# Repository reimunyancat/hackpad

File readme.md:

# Hackpad — 9-Key Macropad

A custom 9-key (3x3 matrix) macropad with a rotary encoder and a 1.3" OLED, built for the Hack Club Stardance Hackpad YSWS.

- **MCU:** Seeed XIAO RP2040
- **Layout:** 3x3 switch matrix + 1 rotary encoder (EC11) + 1.3" 128x64 OLED (I2C)
- **Firmware:** KMK (CircuitPython)
- **Case:** Sandwich-style, fully 3D printed

## Gallery

### Assembled model

### Schematic

### PCB layout

### Case (3D)

## Bill of Materials

| Component | Qty | Notes |
| --- | --- | --- |
| Seeed XIAO RP2040 | 1 | MCU (kit) |
| 1N4148 diode | 9 | matrix anti-ghosting (kit) |
| MX-style switch | 9 | (kit) |
| Kailh MX hotswap socket | 9 | self-sourced |
| EC11 rotary encoder | 1 | 20mm D-shaft (kit) |
| 1.3" 128x64 SH1106 OLED | 1 | I2C, self-sourced |
| 2.54mm 4-pin female header | 1 | OLED mount, self-sourced |
| DSA keycap | 9 | (kit) |
| M3x16 screw | 6 | (kit) |
| M3x5x4 heatset insert | 6 | (kit) |
| Custom PCB | 1 | JLCPCB, 2-layer, ~57x79mm |
| 3D printed case | 1 | top plate + bottom shell |

## Repository structure

```
.
├── README.md
├── CAD/
│   └── assembled-model.STEP
├── PCB/
│   ├── hackpad.kicad_pro
│   ├── hackpad.kicad_sch
│   └── hackpad.kicad_pcb
├── Firmware/
│   └── main.py
└── production/
    ├── gerbers.zip
    ├── Top.STEP
    ├── Bottom.STEP
    └── main.py
```

## Firmware

KMK (CircuitPython). Flash CircuitPython to the XIAO, copy the `kmk` library folder onto the CIRCUITPY drive, then drop `Firmware/main.py` on it.

Pin mapping (taken from the schematic):

- Columns: D0, D1, D2
- Rows: D3, D6, D7
- Encoder: A = D8, B = D9, SW = D10
- OLED I2C: SDA = D4, SCL = D5
- Diode orientation: COL2ROW

## Specs

- PCB: ~57x79mm, 2-layer (limit 100x100mm)
- Case: fully 3D printed (limit 200x200x100mm)
- Inputs: 9 keys + 1 encoder = 10 (limit 16)
- Tolerances: 0.2mm on mating surfaces, M3x5x4 heatset inserts (4.7mm holes), M3x16 screws (3.4mm clearance)

Note: I need a soldering iron — please include the $18 soldering iron grant.

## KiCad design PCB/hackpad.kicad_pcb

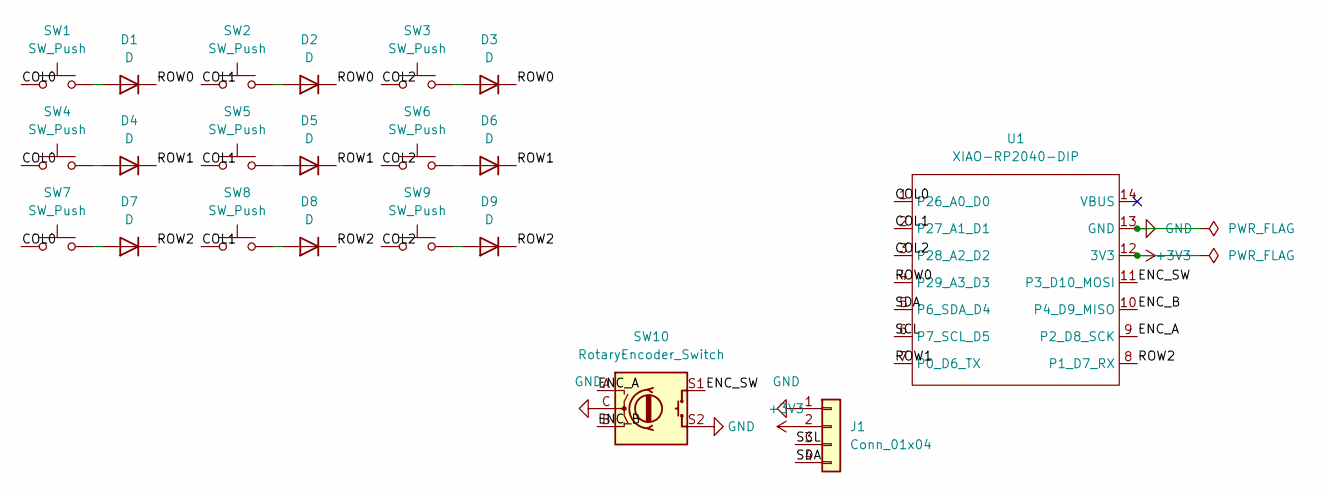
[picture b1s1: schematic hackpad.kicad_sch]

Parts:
D1, D2, D3, D4, D5, D6, D7, D8, D9: D; D_DO-35_SOD27_P7.62mm_Horizontal
J1: Conn_01x04; PinHeader_1x04_P2.54mm_Vertical
SW1, SW2, SW3, SW4, SW5, SW6, SW7, SW8, SW9: SW_Push; Kailh_socket_MX
SW10: RotaryEncoder_Switch; RotaryEncoder_Alps_EC11E-Switch_Vertical_H20mm
U1: XIAO-RP2040-DIP

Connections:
+3V3: J1.2, U1.12 (3V3)
/COL0: SW1.1, SW4.1, SW7.1, U1.1 (P26_A0_D0)
/COL1: SW2.1, SW5.1, SW8.1, U1.2 (P27_A1_D1)
/COL2: SW3.1, SW6.1, SW9.1, U1.3 (P28_A2_D2)
/ENC_A: SW10.A, U1.9 (P2_D8_SCK)
/ENC_B: SW10.B, U1.10 (P4_D9_MISO)
/ENC_SW: SW10.S1, U1.11 (P3_D10_MOSI)
/ROW0: D1.1 (K), D2.1 (K), D3.1 (K), U1.4 (P29_A3_D3)
/ROW1: D4.1 (K), D5.1 (K), D6.1 (K), U1.7 (P0_D6_TX)
/ROW2: D7.1 (K), D8.1 (K), D9.1 (K), U1.8 (P1_D7_RX)
/SCL: J1.3, U1.6 (P7_SCL_D5)
/SDA: J1.4, U1.5 (P6_SDA_D4)
GND: J1.1, SW10.C, SW10.S2, U1.13 (GND)
unnamed: D1.2 (A), SW1.2
unnamed: D2.2 (A), SW2.2
unnamed: D3.2 (A), SW3.2
unnamed: D4.2 (A), SW4.2
unnamed: D5.2 (A), SW5.2
unnamed: D6.2 (A), SW6.2
unnamed: D7.2 (A), SW7.2
unnamed: D8.2 (A), SW8.2
unnamed: D9.2 (A), SW9.2

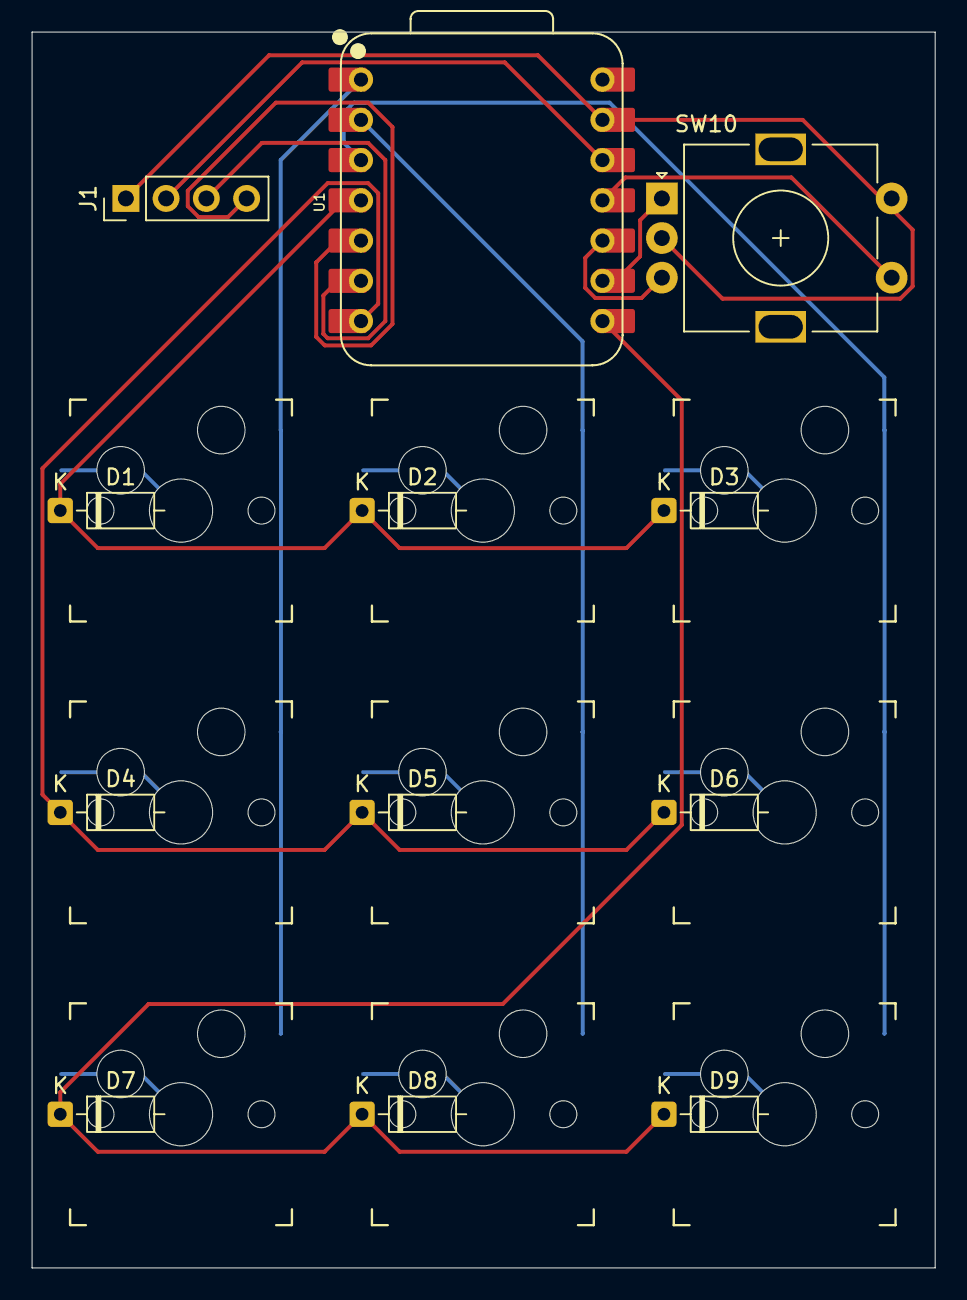
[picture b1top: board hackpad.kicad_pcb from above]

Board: 2 copper layers, 57.0 x 78.0 mm, 21 parts (0 on the bottom side), 22 nets.

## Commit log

2026-06-07 init
2026-06-21 Rename README.md to readme.md
